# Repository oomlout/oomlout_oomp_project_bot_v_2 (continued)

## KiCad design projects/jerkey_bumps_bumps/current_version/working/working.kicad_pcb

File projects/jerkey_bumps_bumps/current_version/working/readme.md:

# bumps
 
## summary 
* id: jerkey_bumps_bumps
* user: jerkey
* name: bumps
* board: bumps
* repo: https://github.com/jerkey/bumps
* src_file_repo_kicad_pcb: bumps.kicad_pcb
* src_file_repo_kicad_pcb_link: https://github.com/jerkey/bumps/tree/master/bumps.kicad_pcb

* src_file_repo_sch: bumps.sch
* src_file_repo_sch_link: https://github.com/jerkey/bumps/tree/master/bumps.sch
* full details link: https://github.com/oomlout/oomlout_oomp_project_bot_v_2/tree/main/projects/jerkey_bumps_bumps/current_version/working

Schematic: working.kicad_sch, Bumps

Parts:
C1, C2, C3, C4, C5, C7, C8: 100u; c_elec_6.3x7.7
C6: 110p; SM0805
C9, C10, C11, C14: 10u; c_elec_4x5.7
C12: 22u; c_elec_5x5.7
C13: 100n; c_0805
C15: 100n; SM0805
D1: SMD-Schottky; Diode-MiniMELF_Standard
D2, D3, D4: 1.8V; Diode-MiniMELF_Standard
D5, D6, D7: BAT54S; SOT23
D8: PWM1; LED-0805
D9: PWM2; LED-0805
D10, D11: SB180; Diode_DO-41_SOD81_Vertical_KathodeUp
D12: E-Up; LED-0805
D13: E-Dn; LED-0805
D14: A-Up; LED-0805
D15: A-Dn; LED-0805
D16: X-Up; LED-0805
D17: X-Dn; LED-0805
D18: Y-Up; LED-0805
D19: Y-Dn; LED-0805
D20: Z-Up; LED-0805
D21: Z-Dn; LED-0805
D22: AUX1; LED-0805
D23: AUX2; LED-0805
D24: 5V; LED-0805
D25: 3.3V; LED-0805
F1: FUSE; Fuse_TE5_Littlefuse-395Series
L1: 68u; INDUCTOR_V; DigiKey RLB0914-680KL
M1, M2, M3: CONN_1; 1pin
P1: Micro-E; Pin_Header_Straight_2x03
P2, P5, P6, P7: DIL6; Pin_Header_Straight_2x03
P3, P4: Mot-E; Pin_Header_Straight_1x04
P8: P8 Header; PIN_ARRAY_23X2
P9: P9 Header; PIN_ARRAY_23X2
P10, P11: Mot-A; Pin_Header_Straight_1x04
P12, P22: Mot-X; Pin_Header_Straight_1x04
P13: T1; Pin_Header_Straight_1x02
P14: T2; Pin_Header_Straight_1x02
P15: T3; Pin_Header_Straight_1x02
P16: MPower; AK300-2
P17: PWM-2; AK300-2
P18: PWM-1; AK300-2
P19: END-X; Pin_Header_Straight_1x02
P20: END-Y; Pin_Header_Straight_1x02
P21: END-Z; Pin_Header_Straight_1x02
P23, P24: Mot-Y; Pin_Header_Straight_1x04
P25, P26: Mot-Z; Pin_Header_Straight_1x04
P27: Aux; Pin_Header_Straight_1x02
P29: PWM; Pin_Header_Straight_1x02
Q1, Q2: N-FET; TO-220_FET-GDS_Vertical_MountedFromLS
Q3, Q4: FDS9926A; SOIC-8_N
R1, R2, R3, R4, R5, R9, R10, R40, R41: 100k; SM0805
R6, R27, R28, R29, R30, R31, R33, R35, R38, R39: 1k; SM0805
R7: 0R3; SM0805
R8: 3k; SM0805
R11, R12: R68; SM0805
R13, R14, R15, R20, R22, R24: 4k7; SM0805
R16, R17, R18, R19, R21, R23, R32, R34, R36, R37: 68; SM0805
R25, R26: 2k2; SM0805
U1: E-Polo; POLOLU
U2: A-Polo; POLOLU
U3: X-Polo; POLOLU
U4: Y-Polo; POLOLU
U5: Z-Polo; POLOLU
U6: MC34063; SOIC-8_N
U7: AP1117/3.3; SOT-223-3

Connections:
AGND: C9.2, C10.2, C11.2, C13.2, C14.2, D2.1, D3.1, D4.1, P9.33 (AIN4), P9.34 (AGND), P9.35 (AIN6), P9.36 (AIN5), P9.38 (AIN3), P13.1, P14.1, P15.1
AUX_1: P9.11 (GPIO0_30), R32.1, R33.1
AUX_2: P9.13 (GPIO0_31), R34.1, R35.1
DIR_A: P9.15 (GPIO1_16), R28.2, U2.8 (DIR)
DIR_B: P9.23 (GPIO1_17)
DIR_C: P9.14 (GPIO1_18)
DIR_E: P8.15 (GPIO1_15), R27.2, U1.8 (DIR)
DIR_U: P9.16 (GPIO1_19)
DIR_X: P8.12 (GPIO1_12), R29.2, U3.8 (DIR)
DIR_Y: P8.11 (GPIO1_13), R30.2, U4.8 (DIR)
DIR_Z: P8.16 (GPIO1_14), R31.2, U5.8 (DIR)
END_X: D5.3, P8.13 (GPIO0_23), R19.2, R20.1
END_Y: D6.3, P8.14 (GPIO0_26), R21.2, R22.1
END_Z: D7.3, P8.17 (GPIO0_27), R23.2, R24.1
GND: C1.2, C2.2, C3.2, C4.2, C5.2, C6.2, C7.2, C8.2, C12.2, C15.2, D1.1, D5.1, D6.1, D7.1, D13.2, D15.2, D17.2, D19.2, D21.2, D22.2, D23.2, D24.2, D25.2, P8.1 (GND), P8.2 (GND), P9.1 (GND), P9.2 (GND), P9.43 (GND), P9.44 (GND), P9.45 (GND), P9.46 (GND), P16.2, P19.2, P20.2, P21.2, Q1.S, Q2.S, Q3.1, Q3.3, Q4.1, Q4.3, R1.1, R2.1, R3.1, R4.1, R5.1, R6.2, R9.1, R10.2, R40.2, R41.2, U1.9 (GND), U1.15 (GND), U2.9 (GND), U2.15 (GND), U3.9 (GND), U3.15 (GND), U4.9 (GND), U4.15 (GND), U5.9 (GND), U5.15 (GND), U6.4, U7.1 (GND)
unnamed: C6.1, U6.3
unnamed: C9.1, P13.2, R13.1, R16.2
unnamed: C10.1, P14.2, R14.1, R17.2
unnamed: C11.1, P15.2, R15.1, R18.2
unnamed: D1.2, L1.1, U6.2
unnamed: D8.1, R25.2
unnamed: D9.1, R26.2
unnamed: D8.2, D10.1, P18.2, Q1.D
unnamed: D9.2, D11.1, P17.2, Q2.D
unnamed: D12.2, D13.1, R27.1
unnamed: D14.2, D15.1, R28.1
unnamed: D16.2, D17.1, R29.1
unnamed: D18.2, D19.1, R30.1
unnamed: D20.2, D21.1, R31.1
unnamed: D22.1, R33.2
unnamed: D23.1, R35.2
unnamed: D24.1, R38.1
unnamed: D25.1, R39.1
unnamed: F1.1, P16.1
unnamed: P1.1, R1.2, U1.2 (MS1)
unnamed: P1.2, U1.3 (MS2)
unnamed: P1.3, U1.4 (MS3)
unnamed: P2.1, R2.2, U2.2 (MS1)
unnamed: P2.2, U2.3 (MS2)
unnamed: P2.3, U2.4 (MS3)
unnamed: P3.1, P4.1, U1.14 (2B)
unnamed: P3.2, P4.2, U1.13 (2A)
unnamed: P3.3, P4.3, U1.12 (1A)
unnamed: P3.4, P4.4, U1.11 (1B)
unnamed: P5.1, R3.2, U3.2 (MS1)
unnamed: P5.2, U3.3 (MS2)
unnamed: P5.3, U3.4 (MS3)
unnamed: P6.1, R4.2, U4.2 (MS1)
unnamed: P6.2, U4.3 (MS2)
unnamed: P6.3, U4.4 (MS3)
unnamed: P7.1, R5.2, U5.2 (MS1)
unnamed: P7.2, U5.3 (MS2)
unnamed: P7.3, U5.4 (MS3)
unnamed: P10.1, P11.1, U2.14 (2B)
unnamed: P10.2, P11.2, U2.13 (2A)
unnamed: P10.3, P11.3, U2.12 (1A)
unnamed: P10.4, P11.4, U2.11 (1B)
unnamed: P12.1, P22.1, U3.14 (2B)
unnamed: P12.2, P22.2, U3.13 (2A)
unnamed: P12.3, P22.3, U3.12 (1A)
unnamed: P12.4, P22.4, U3.11 (1B)
unnamed: P19.1, R19.1
unnamed: P20.1, R21.1
unnamed: P21.1, R23.1
unnamed: P23.1, P24.1, U4.14 (2B)
unnamed: P23.2, P24.2, U4.13 (2A)
unnamed: P23.3, P24.3, U4.12 (1A)
unnamed: P23.4, P24.4, U4.11 (1B)
unnamed: P25.1, P26.1, U5.14 (2B)
unnamed: P25.2, P26.2, U5.13 (2A)
unnamed: P25.3, P26.3, U5.12 (1A)
unnamed: P25.4, P26.4, U5.11 (1B)
unnamed: P27.1, Q3.7, Q3.8
unnamed: P27.2, Q3.5, Q3.6
unnamed: P29.1, Q4.7, Q4.8
unnamed: P29.2, Q4.5, Q4.6
unnamed: Q1.G, R9.2, R11.2
unnamed: Q2.G, R10.1, R12.1
unnamed: Q3.2, R32.2
unnamed: Q3.4, R34.2
unnamed: Q4.2, R36.2, R40.1
unnamed: Q4.4, R37.2, R41.1
unnamed: R6.1, R8.2, U6.5
unnamed: R7.1, U6.1, U6.7, U6.8
unnamed: U1.5 (~RESET), U1.6 (~SLEEP)
unnamed: U2.5 (~RESET), U2.6 (~SLEEP)
unnamed: U3.5 (~RESET), U3.6 (~SLEEP)
unnamed: U4.5 (~RESET), U4.6 (~SLEEP)
unnamed: U5.5 (~RESET), U5.6 (~SLEEP)
PWM_1: P8.9 (GPIO2_05), R11.1
PWM_2: P8.10 (GPIO2_04), R12.2
PWM_3: P8.7 (GPIO2_02), R36.1
PWM_4: P8.8 (GPIO2_03), R37.1
STEP_A: P9.42 (GPIO0_07), U2.7 (STEP)
STEP_B: P9.26 (GPIO0_14)
STEP_C: P9.24 (GPIO0_15)
STEP_E: P9.17 (GPIO0_05), U1.7 (STEP)
STEP_U: P9.41 (GPIO0_20)
STEP_X: P9.22 (GPIO0_02), U3.7 (STEP)
STEP_Y: P9.21 (GPIO0_03), U4.7 (STEP)
STEP_Z: P9.18 (GPIO0_04), U5.7 (STEP)
TEMP_1: D2.2, P9.39 (AIN0), R16.1
TEMP_2: D3.2, P9.40 (AIN1), R17.1
TEMP_3: D4.2, P9.37 (AIN2), R18.1
VDD_3V3: C12.1, D5.2, D6.2, D7.2, D12.1, D14.1, D16.1, D18.1, D20.1, P1.4, P1.5, P1.6, P2.4, P2.5, P2.6, P5.4, P5.5, P5.6, P6.4, P6.5, P6.6, P7.4, P7.5, P7.6, R20.2, R22.2, R24.2, R39.2, U1.10 (VDD), U2.10 (VDD), U3.10 (VDD), U4.10 (VDD), U5.10 (VDD), U7.2 (Vout)
VDD_5V: C8.1, L1.2, P9.5 (VDD_5V), P9.6 (VDD_5V), R8.1, R38.2, U7.3 (VIN)
VDD_ADC: C13.1, C14.1, P9.32 (VDD_ADC), R13.2, R14.2, R15.2
VMOT: C1.1, C2.1, C3.1, C4.1, C5.1, C7.1, C15.1, D10.2, D11.2, F1.2, P17.1, P18.1, R7.2, R25.1, R26.1, U1.16 (VMOT), U2.16 (VMOT), U3.16 (VMOT), U4.16 (VMOT), U5.16 (VMOT), U6.6
~EN: P9.12 (GPIO1_28), U1.1 (~ENABLE), U2.1 (~ENABLE), U3.1 (~ENABLE), U4.1 (~ENABLE), U5.1 (~ENABLE)

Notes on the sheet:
place one capacitor near each motor controller
Temperature input
Endswitches
Power PWM
Aux, Open Collector
Switching Power Supply 5V
100n capacitor must be close
100n capacitor must be close
PWM, Open Collector
capacitors on LEDs accentuate voltage transients
Supply 3.3V

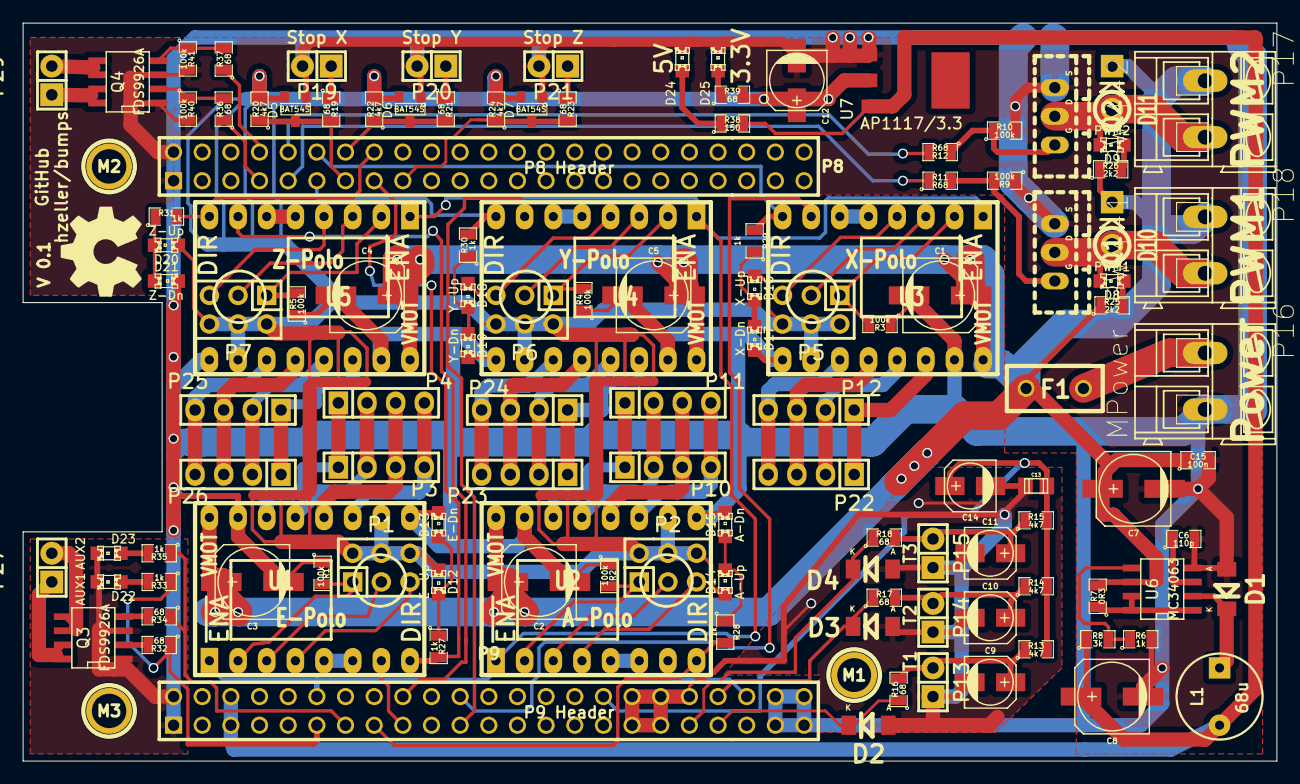
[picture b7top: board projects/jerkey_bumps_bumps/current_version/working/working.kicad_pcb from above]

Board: 2 copper layers, 111.1 x 65.4 mm, 125 parts (0 on the bottom side), 103 nets.
